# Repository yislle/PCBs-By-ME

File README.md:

# PCBs-By-ME
Proyectos electrónicos

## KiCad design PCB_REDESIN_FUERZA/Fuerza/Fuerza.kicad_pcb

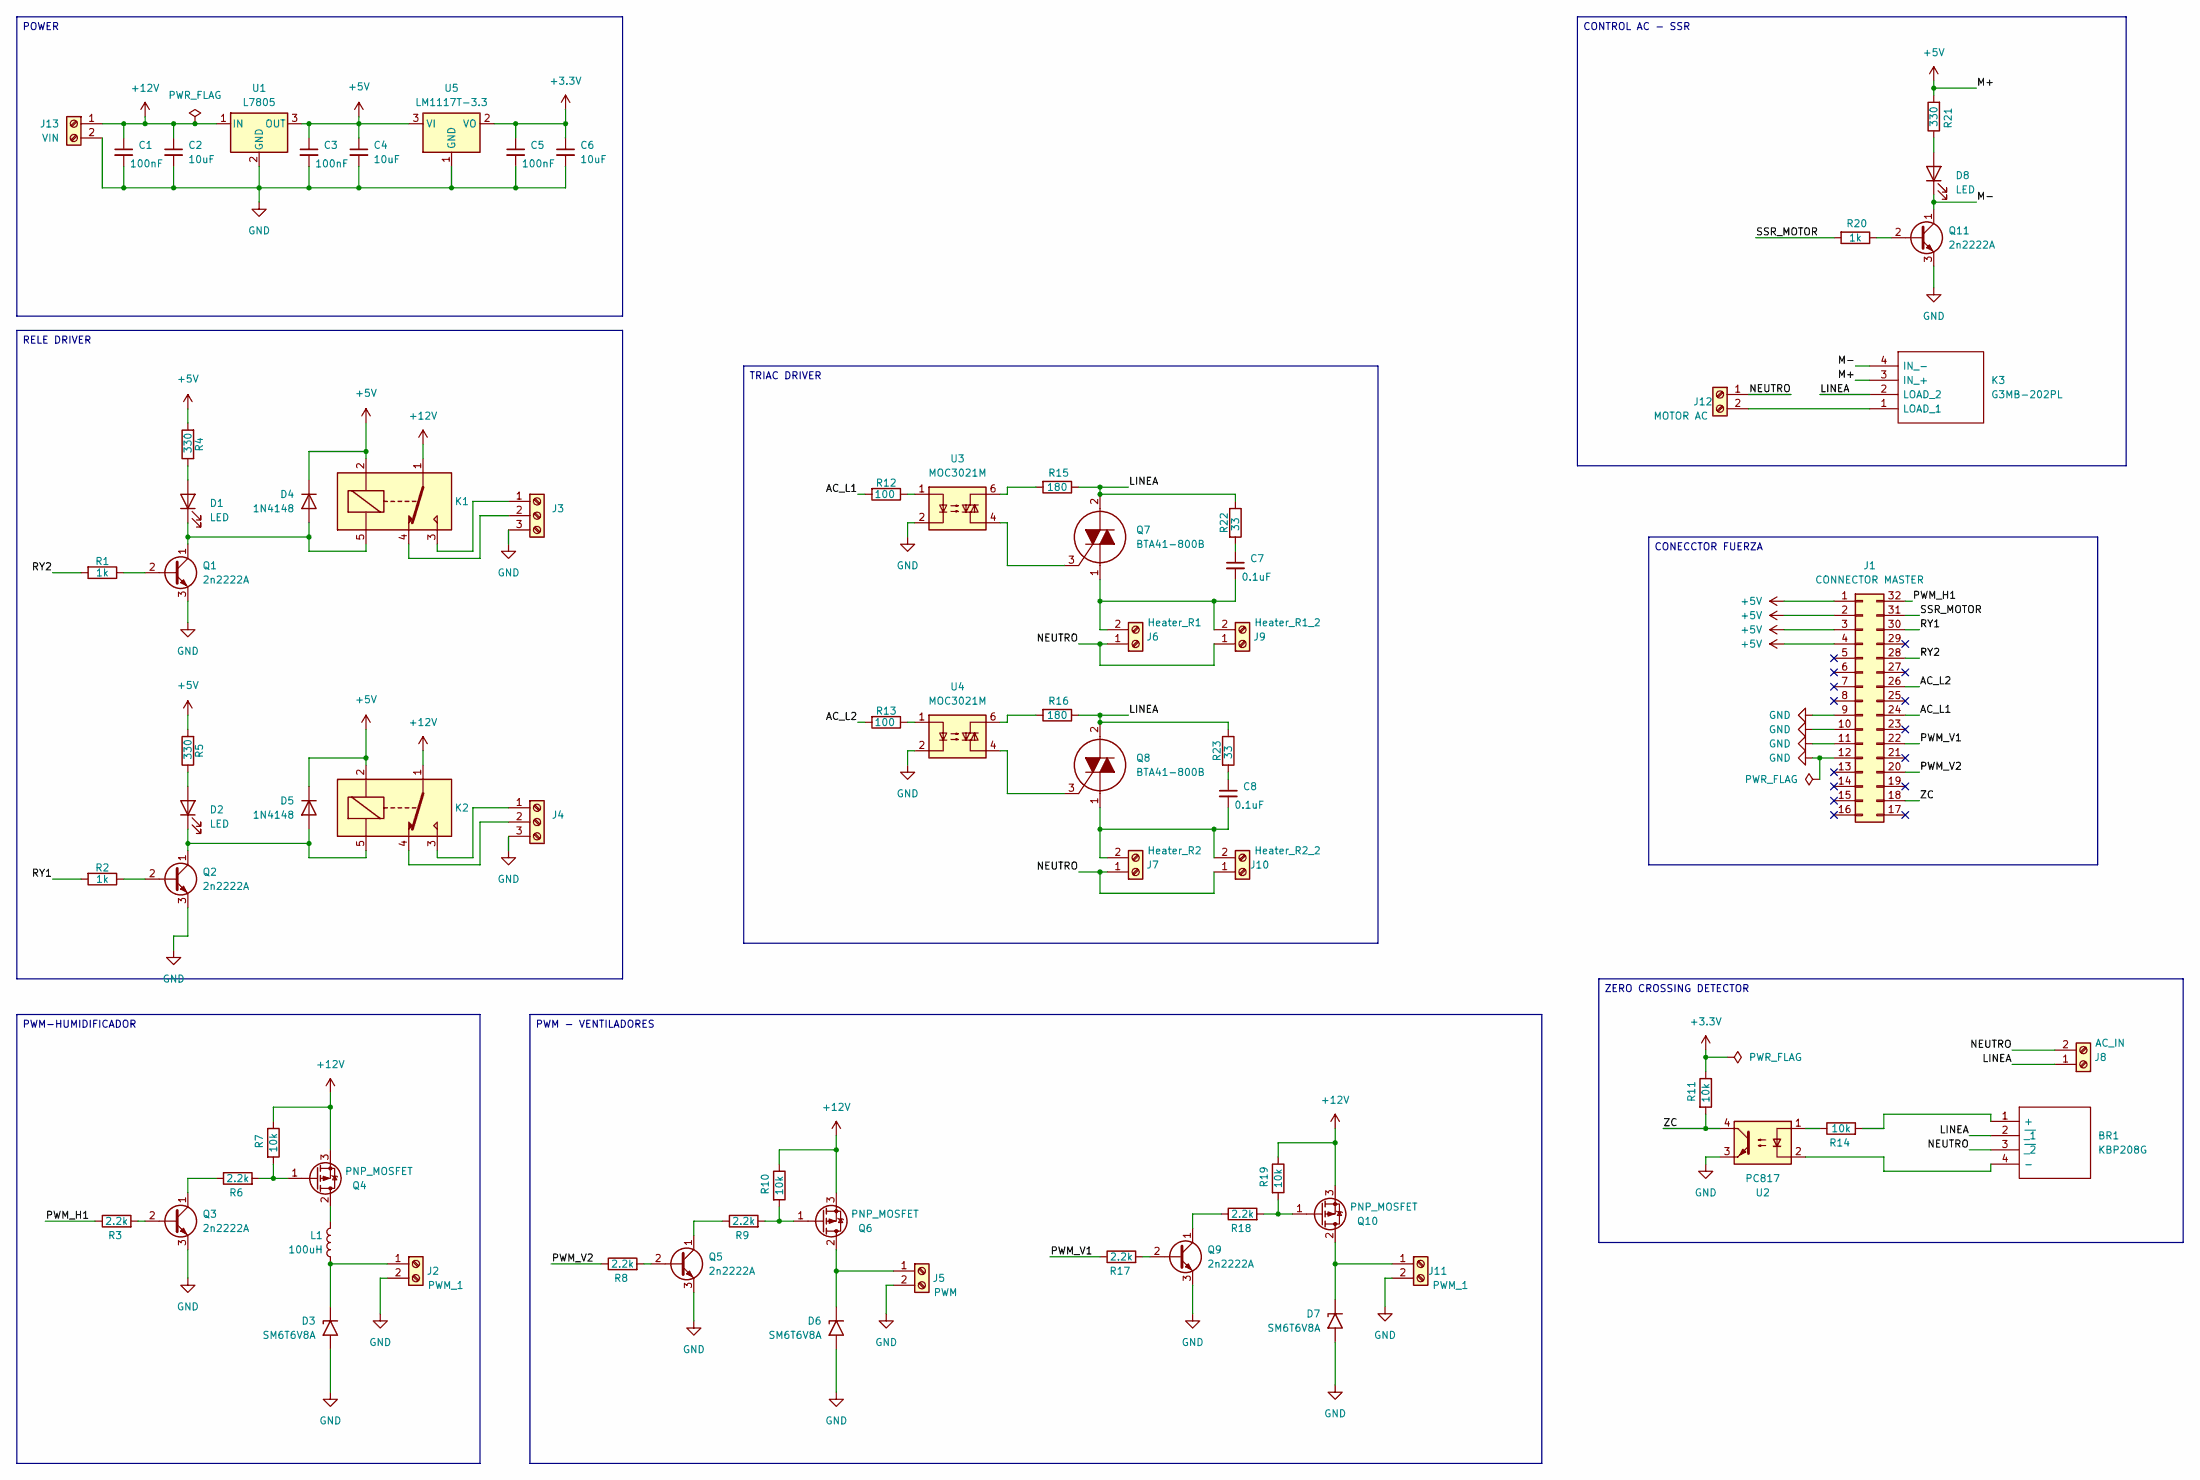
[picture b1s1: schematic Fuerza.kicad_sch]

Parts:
BR1: KBP208G; Manufacturer_Part_Number KBP208G; Mouser Part Number 621-KBP208G
C1, C3, C5: 100nF; C_1206_3216Metric_Pad1.33x1.80mm_HandSolder
C2, C4, C6: 10uF; C_1206_3216Metric_Pad1.33x1.80mm_HandSolder
C7, C8: 0.1uF; C_Rect_L13.0mm_W3.0mm_P10.00mm_FKS3_FKP3_MKS4
D1, D2, D8: LED; LED_1206_3216Metric
D3, D6, D7: SM6T6V8A; D_SMB
D4, D5: 1N4148; D_SMB_Handsoldering
J1: CONNECTOR MASTER; PinHeader_2x16_P2.54mm_Vertical
J2, J11: PWM_1; TerminalBlock_Phoenix_MKDS-1,5-2-5.08_1x02_P5.08mm_Horizont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
J3, J4: Screw_Terminal_01x03; TerminalBlock_MetzConnect_Type011_RT05503HBLC_1x03_P5.00mm_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
J5: PWM; TerminalBlock_Phoenix_MKDS-1,5-2-5.08_1x02_P5.08mm_Horizont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
J6: Heater_R1; NC6P10702
J7: Heater_R2; NC6P10702
J8: AC_IN; NC6P10702
J9: Heater_R1_2; NC6P10702
J10: Heater_R2_2; NC6P10702
J12: MOTOR AC; NC6P10702
J13: VIN; TerminalBlock_Phoenix_MKDS-1,5-2-5.08_1x02_P5.08mm_Horizont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
K1, K2: SANYOU_SRD_Form_C; Relay_SPDT_SANYOU_SRD_Series_Form_C
K3: G3MB-202PL; G3MB202PL; Manufacturer_Part_Number G3MB-202PL
L1: 100uH; L_Sunlord_MWSA0518S
Q1, Q2, Q3, Q5, Q9, Q11: 2n2222A; TO-92_Inline
Q4, Q6, Q10: PNP_MOSFET; TO-252-2
Q7, Q8: BTA41-800B; TO552P460X1530X2215-3P; Manufacturer_Part_Number BTA41-800B; Mouser Part Number N/A
R1, R2, R20: 1k; R_0805_2012Metric
R3, R6, R8, R9, R17, R18: 2.2k; R_0805_2012Metric
R4, R5, R21: 330; R_0805_2012Metric
R7, R10, R11, R14, R19: 10k; R_0805_2012Metric
R12, R13: 100; R_0805_2012Metric
R15, R16: 180; R_Axial_DIN0414_L11.9mm_D4.5mm_P15.24mm_Horizontal
R22, R23: 33; R_Axial_Power_L48.0mm_W12.5mm_P10.16mm_Vertical
U1: L7805; TO-252-2
U2: PC817; DIP-4_W7.62mm
U3, U4: MOC3021M; DIP-6_W7.62mm_Socket_LongPads
U5: LM1117T-3.3; TO-220F-3_Horizontal_TabDown

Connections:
+3.3V: C5.1, C6.1, R11.1, U5.2 (VO)
+5V: C3.1, C4.1, D4.1 (K), D5.1 (K), J1.1, J1.2, J1.3, J1.4, K1.2, K2.2, K3.3 (IN_+), R4.2, R5.2, R21.2, U1.3 (OUT), U5.3 (VI)
+12V: C1.1, C2.1, J13.1, K1.1, K2.1, Q4.3 (S), Q6.3 (S), Q10.3 (S), R7.1, R10.1, R19.1, U1.1 (IN)
/AC_L1: J1.24, R12.2
/AC_L2: J1.26, R13.2
/LINEA: BR1.2 (~_1), J8.1, K3.2 (LOAD_2), Q7.2, Q8.2, R15.1, R16.1, R22.1, R23.1
/M-: D8.1 (K), K3.4 (IN_-), Q11.1 (C)
/NEUTRO: BR1.3 (~_2), J6.1, J7.1, J8.2, J9.1, J10.1, J12.1
/PWM_H1: J1.32, R3.1
/PWM_V1: J1.22, R17.1
/PWM_V2: J1.20, R8.1
/RY1: J1.30, R2.2
/RY2: J1.28, R1.2
/SSR_MOTOR: J1.31, R20.2
/ZC: J1.18, R11.2, U2.4
GND: C1.2, C2.2, C3.2, C4.2, C5.2, C6.2, D3.2 (A2), D6.2 (A2), D7.2 (A2), J1.9, J1.10, J1.11, J1.12, J2.2, J3.3, J4.3, J5.2, J11.2, J13.2, Q1.3 (E), Q2.3 (E), Q3.3 (E), Q5.3 (E), Q9.3 (E), Q11.3 (E), U1.2 (GND), U2.3, U3.2, U4.2, U5.1 (GND)
unnamed: BR1.1 (+), R14.2
unnamed: BR1.4 (-), U2.2
unnamed: C7.1, R22.2
unnamed: C8.1, R23.2
unnamed: D1.2 (A), R4.1
unnamed: D1.1 (K), D4.2 (A), K1.5, Q1.1 (C)
unnamed: D2.2 (A), R5.1
unnamed: D2.1 (K), D5.2 (A), K2.5, Q2.1 (C)
unnamed: D3.1 (A1), J2.1, L1.2
unnamed: D6.1 (A1), J5.1, Q6.2 (D)
unnamed: D7.1 (A1), J11.1, Q10.2 (D)
unnamed: D8.2 (A), R21.1
unnamed: J3.1, K1.3
unnamed: J3.2, K1.4
unnamed: J4.1, K2.3
unnamed: J4.2, K2.4
unnamed: C7.2, J6.2, J9.2, Q7.1
unnamed: C8.2, J7.2, J10.2, Q8.1
unnamed: J12.2, K3.1 (LOAD_1)
unnamed: Q1.2 (B), R1.1
unnamed: Q2.2 (B), R2.1
unnamed: Q3.2 (B), R3.2
unnamed: Q3.1 (C), R6.1
unnamed: L1.1, Q4.2 (D)
unnamed: Q4.1 (G), R6.2, R7.2
unnamed: Q5.2 (B), R8.2
unnamed: Q5.1 (C), R9.1
unnamed: Q6.1 (G), R9.2, R10.2
unnamed: Q7.3, U3.4
unnamed: Q8.3, U4.4
unnamed: Q9.2 (B), R17.2
unnamed: Q9.1 (C), R18.1
unnamed: Q10.1 (G), R18.2, R19.2
unnamed: Q11.2 (B), R20.1
unnamed: R12.1, U3.1
unnamed: R13.1, U4.1
unnamed: R14.1, U2.1
unnamed: R15.2, U3.6
unnamed: R16.2, U4.6

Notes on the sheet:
RELE DRIVER
CONTROL AC - SSR
PWM-HUMIDIFICADOR
ZERO CROSSING DETECTOR
TRIAC DRIVER
CONECCTOR FUERZA
POWER
PWM - VENTILADORES

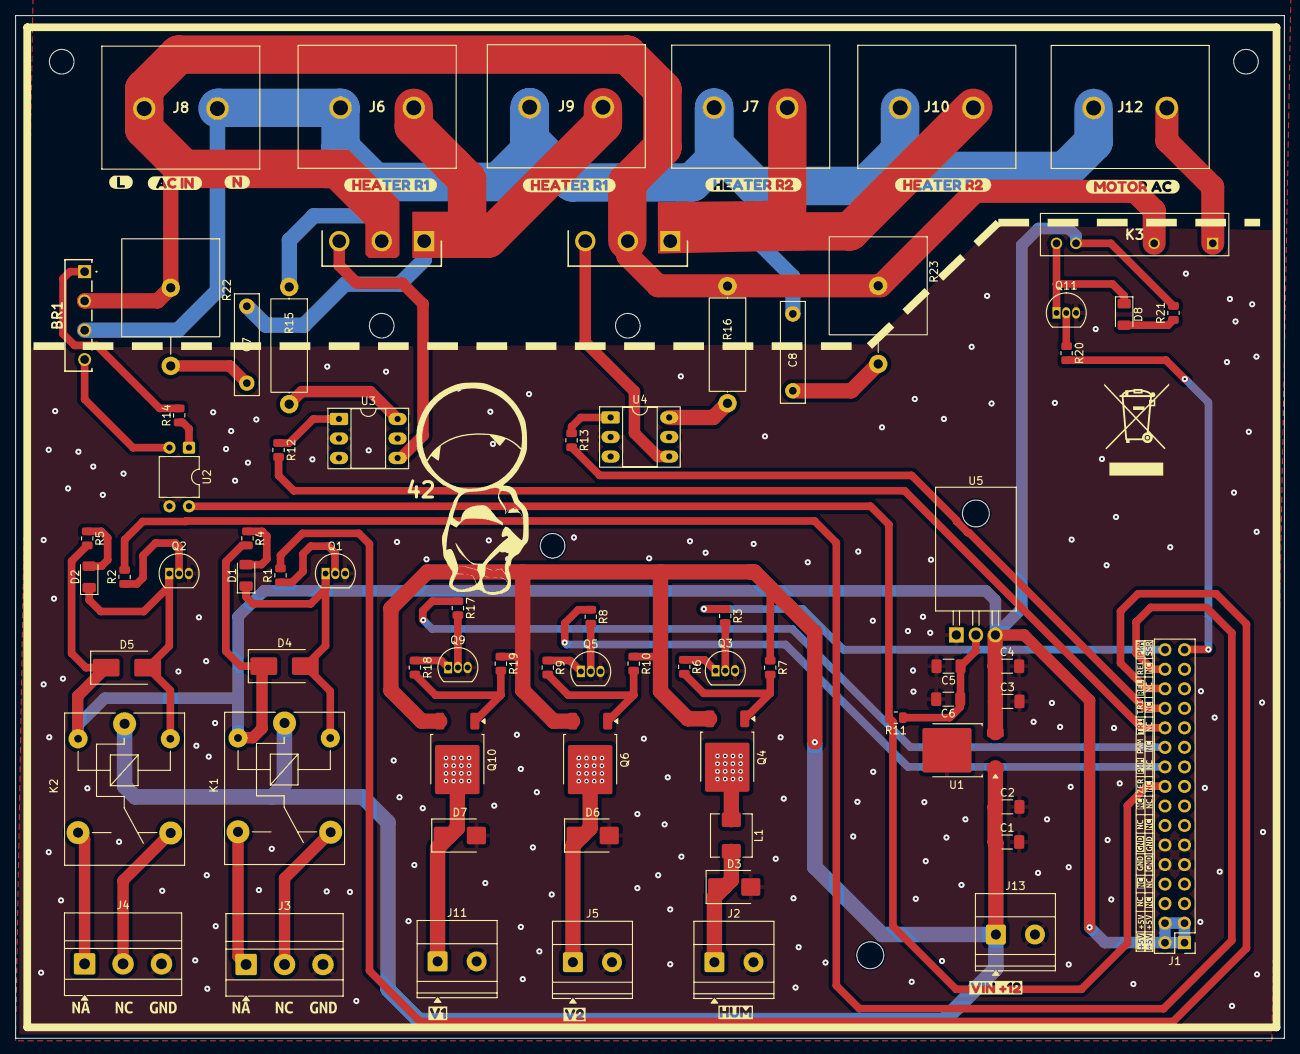
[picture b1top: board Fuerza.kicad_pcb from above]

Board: 2 copper layers, 165.0 x 133.0 mm, 124 parts (0 on the bottom side), 55 nets.

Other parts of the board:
42: LOGO
kibuzzard-6933B8AD, kibuzzard-6933B8AD#2: G***; kibuzzard-6933B8AD
kibuzzard-6933B8B3, kibuzzard-6933B8B3#2: G***; kibuzzard-6933B8B3
kibuzzard-6933B8C0, kibuzzard-6933B8C0#2: G***; kibuzzard-6933B8C0
kibuzzard-69101CAE, kibuzzard-69101CAE#2: G***; kibuzzard-69101CAE
kibuzzard-69101CCC, kibuzzard-69101CCC#2, kibuzzard-69101CCC#3, kibuzzard-69101CCC#4, kibuzzard-69101CCC#5, kibuzzard-69101CCC#6, kibuzzard-69101CCC#7: G***; kibuzzard-69101CCC
kibuzzard-69101D02: G***; kibuzzard-69101D02
kibuzzard-69101D2A, kibuzzard-69101D2A#2, kibuzzard-69101D2A#3, kibuzzard-69101D2A#4, kibuzzard-69101D2A#5, kibuzzard-69101D2A#6, kibuzzard-69101D2A#7, kibuzzard-69101D2A#8: G***; kibuzzard-69101D2A
kibuzzard-69101D16: G***; kibuzzard-69101D16
kibuzzard-69101D36: G***; kibuzzard-69101D36
kibuzzard-69101DDA: G***; kibuzzard-69101DDA
kibuzzard-69101DF9: G***; kibuzzard-69101DF9
kibuzzard-69101E1F: G***; kibuzzard-69101E1F
kibuzzard-69101E3D: G***; kibuzzard-69101E3D
kibuzzard-69101E6F: G***; kibuzzard-69101E6F
kibuzzard-69101ED2, kibuzzard-69101ED2#2: G***; kibuzzard-69101ED2
kibuzzard-69101EFC, kibuzzard-69101EFC#2: G***; kibuzzard-69101EFC
kibuzzard-69102CE6: G***; kibuzzard-69102CE6
kibuzzard-693906A7: G***; kibuzzard-693906A7
kibuzzard-693907B1: G***; kibuzzard-693907B1
kibuzzard-693907E1: G***; kibuzzard-693907E1
kibuzzard-693907F7: G***; kibuzzard-693907F7
kibuzzard-6910205B, kibuzzard-6910205B#2: G***; kibuzzard-6910205B
kibuzzard-6939064C: G***; kibuzzard-6939064C
kibuzzard-6939067E: G***; kibuzzard-6939067E
kibuzzard-6939072C: G***; kibuzzard-6939072C
kibuzzard-6939079C: G***; kibuzzard-6939079C
kibuzzard-69390653: G***; kibuzzard-69390653
kibuzzard-69390751, kibuzzard-69390751#2: G***; kibuzzard-69390751
kibuzzard-69390791: G***; kibuzzard-69390791

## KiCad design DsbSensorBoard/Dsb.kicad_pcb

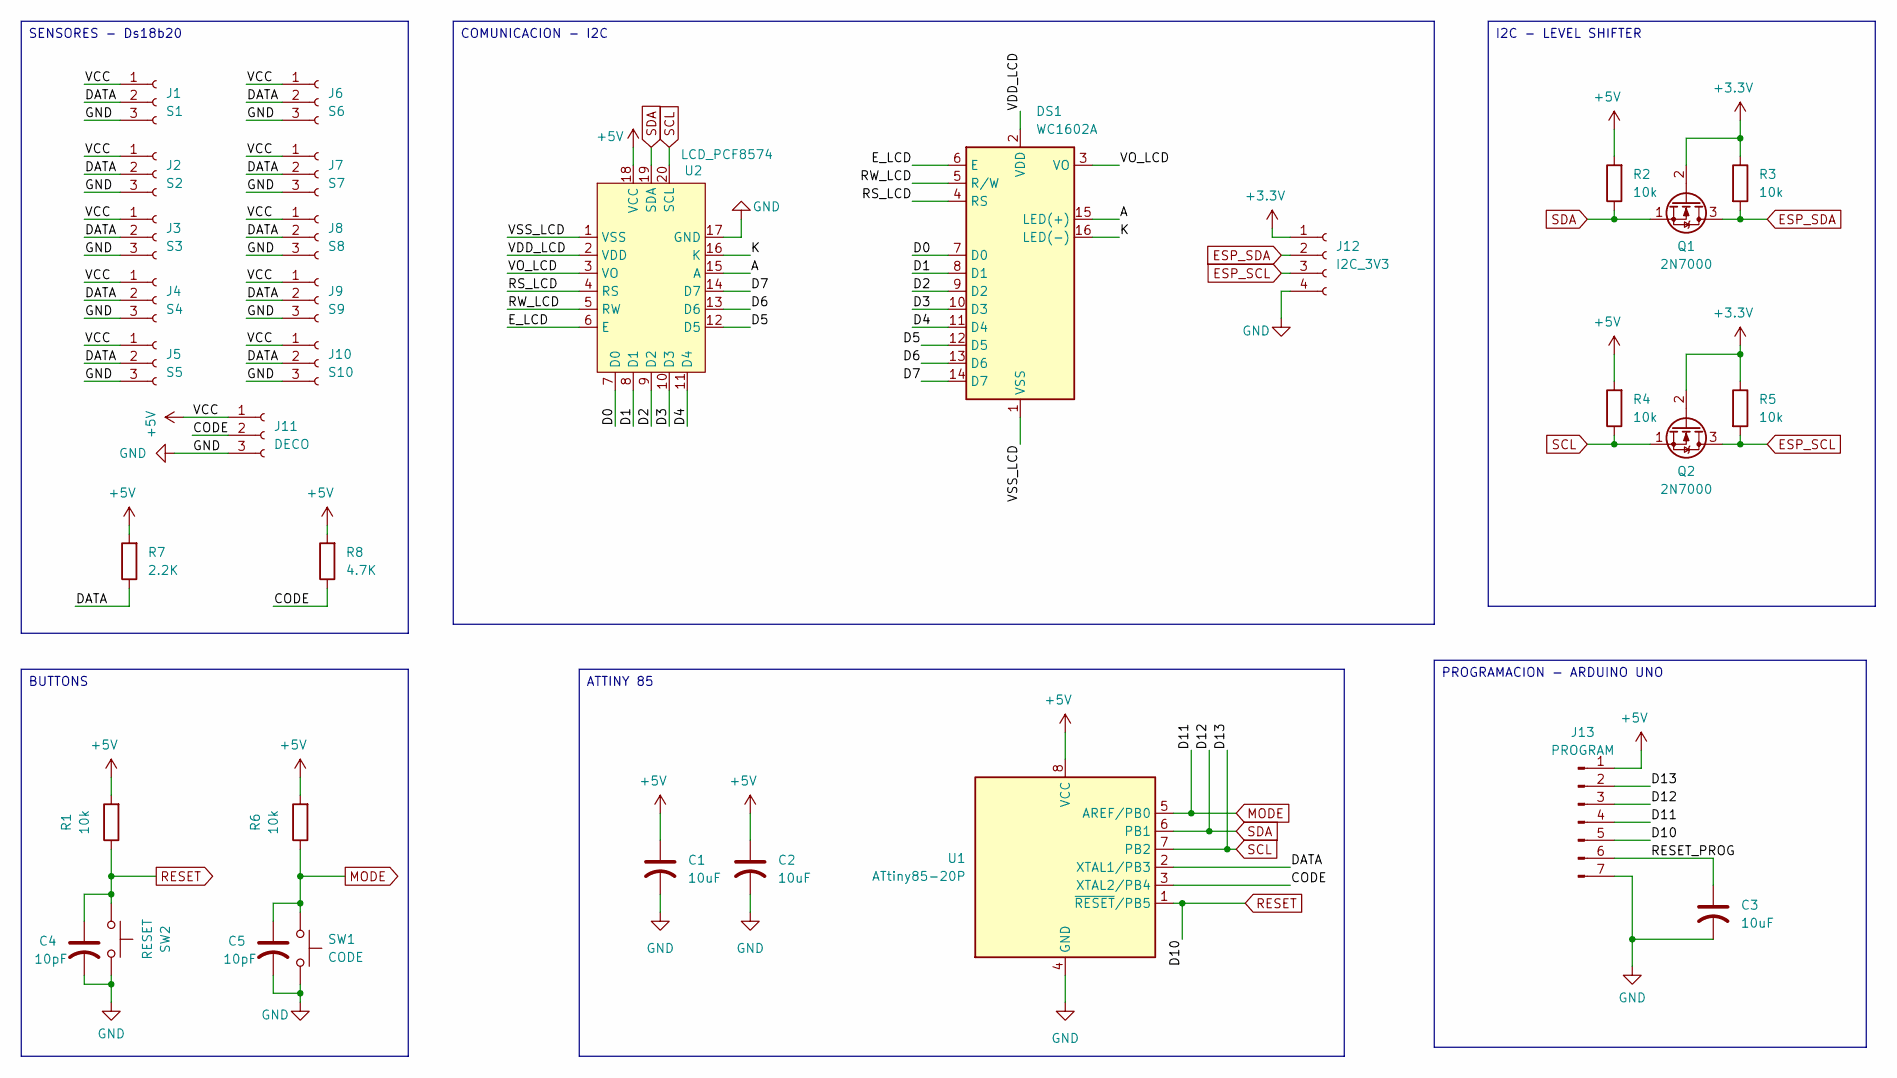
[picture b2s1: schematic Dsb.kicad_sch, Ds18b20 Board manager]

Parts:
C1, C2, C3: 10uF; CP_Radial_D6.3mm_P2.50mm
C4, C5: 10pF; C_Disc_D3.0mm_W1.6mm_P2.50mm
DS1: WC1602A
J1: S1; JST_EH_B3B-EH-A_1x03_P2.50mm_Vertical
J2: S2; JST_EH_B3B-EH-A_1x03_P2.50mm_Vertical
J3: S3; JST_EH_B3B-EH-A_1x03_P2.50mm_Vertical
J4: S4; JST_EH_B3B-EH-A_1x03_P2.50mm_Vertical
J5: S5; JST_EH_B3B-EH-A_1x03_P2.50mm_Vertical
J6: S6; JST_EH_B3B-EH-A_1x03_P2.50mm_Vertical
J7: S7; JST_EH_B3B-EH-A_1x03_P2.50mm_Vertical
J8: S8; JST_EH_B3B-EH-A_1x03_P2.50mm_Vertical
J9: S9; JST_EH_B3B-EH-A_1x03_P2.50mm_Vertical
J10: S10; JST_EH_B3B-EH-A_1x03_P2.50mm_Vertical
J11: DECO; JST_EH_B3B-EH-A_1x03_P2.50mm_Vertical
J12: I2C_3V3; JST_EH_B4B-EH-A_1x04_P2.50mm_Vertical
J13: PROGRAM; PinHeader_1x07_P2.54mm_Vertical
Q1, Q2: 2N7000; TO-92
R1, R2, R3, R4, R5, R6: 10k; R_Axial_DIN0207_L6.3mm_D2.5mm_P15.24mm_Horizontal
R7: 2.2K; R_Axial_DIN0207_L6.3mm_D2.5mm_P15.24mm_Horizontal
R8: 4.7K; R_Axial_DIN0207_L6.3mm_D2.5mm_P15.24mm_Horizontal
SW1: CODE; SW_PUSH_6mm_H4.3mm
SW2: RESET; SW_PUSH_6mm_H4.3mm
U1: ATtiny85-20P; DIP-8_W7.62mm_LongPads
U2: LCD_PCF8574

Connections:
+3.3V: J12.1, Q1.2 (G), Q2.2 (G), R3.1, R5.1
+5V: C1.1, C2.1, J1.1, J2.1, J3.1, J4.1, J5.1, J6.1, J7.1, J8.1, J9.1, J10.1, J11.1, J13.1, R1.2, R2.2, R4.2, R6.2, R7.2, R8.2, U1.8 (VCC), U2.18 (VCC)
/A: DS1.15 (LED(+)), U2.15 (A)
/CODE: J11.2, R8.1, U1.3 (XTAL2/PB4)
/D0: DS1.7 (D0), U2.7 (D0)
/D1: DS1.8 (D1), U2.8 (D1)
/D2: DS1.9 (D2), U2.9 (D2)
/D3: DS1.10 (D3), U2.10 (D3)
/D4: DS1.11 (D4), U2.11 (D4)
/D5: DS1.12 (D5), U2.12 (D5)
/D6: DS1.13 (D6), U2.13 (D6)
/D7: DS1.14 (D7), U2.14 (D7)
/DATA: J1.2, J2.2, J3.2, J4.2, J5.2, J6.2, J7.2, J8.2, J9.2, J10.2, R7.1, U1.2 (XTAL1/PB3)
/E_LCD: DS1.6 (E), U2.6 (E)
/K: DS1.16 (LED(-)), U2.16 (K)
/RESET_PROG: C3.1, J13.6
/RS_LCD: DS1.4 (RS), U2.4 (RS)
/RW_LCD: DS1.5 (R/W), U2.5 (RW)
/VDD_LCD: DS1.2 (VDD), U2.2 (VDD)
/VO_LCD: DS1.3 (VO), U2.3 (VO)
/VSS_LCD: DS1.1 (VSS), U2.1 (VSS)
ESP_SCL: J12.3, Q2.3 (D), R5.2
ESP_SDA: J12.2, Q1.3 (D), R3.2
GND: C1.2, C2.2, C3.2, C4.2, C5.2, J1.3, J2.3, J3.3, J4.3, J5.3, J6.3, J7.3, J8.3, J9.3, J10.3, J11.3, J12.4, J13.7, SW1.2, SW2.1, U1.4 (GND), U2.17 (GND)
MODE: C5.1, J13.4, R6.1, SW1.1, U1.5 (AREF/PB0)
RESET: C4.1, J13.5, R1.1, SW2.2, U1.1 (~RESET/PB5)
SCL: J13.2, Q2.1 (S), R4.1, U1.7 (PB2), U2.20 (SCL)
SDA: J13.3, Q1.1 (S), R2.1, U1.6 (PB1), U2.19 (SDA)

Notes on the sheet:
SENSORES - Ds18b20
ATTINY 85
PROGRAMACION - ARDUINO UNO
BUTTONS
I2C - LEVEL SHIFTER
COMUNICACION - I2C

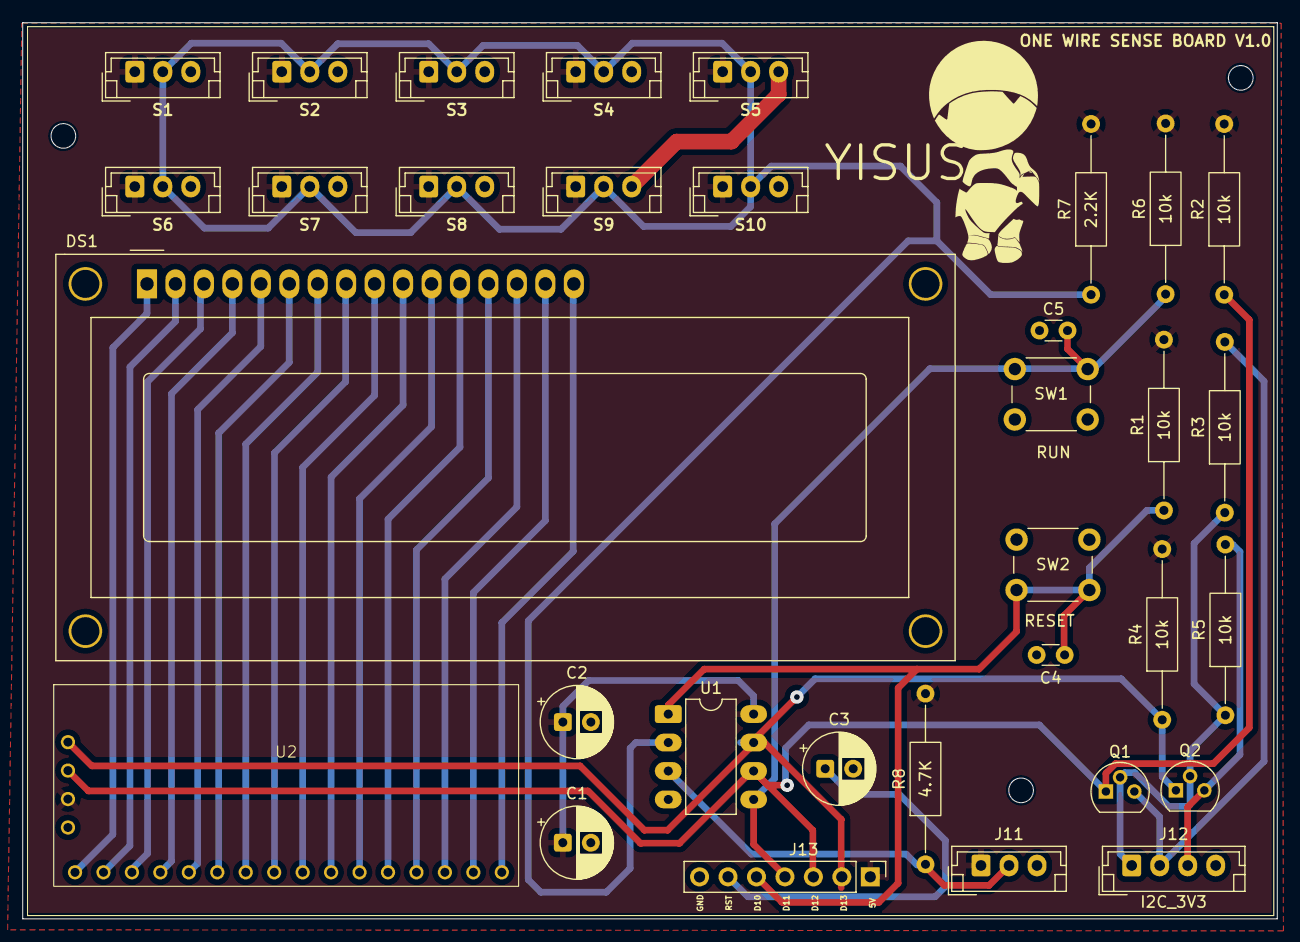
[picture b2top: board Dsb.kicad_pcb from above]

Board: 2 copper layers, 112.0 x 80.0 mm, 34 parts (0 on the bottom side), 28 nets.

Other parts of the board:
YISUS: LOGO

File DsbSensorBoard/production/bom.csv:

Designator,Footprint,Quantity,Value,LCSC Part #
"C1, C2, C3",CP_Radial_D6.3mm_P2.50mm,3,10uF,
"C4, C5",C_Disc_D3.0mm_W1.6mm_P2.50mm,2,10pF,
DS1,WC1602A,1,WC1602A,
J1,JST_EH_B3B-EH-A_1x03_P2.50mm_Vertical,1,S1,
J10,JST_EH_B3B-EH-A_1x03_P2.50mm_Vertical,1,S10,
J11,JST_EH_B3B-EH-A_1x03_P2.50mm_Vertical,1,DECO,
J12,JST_EH_B4B-EH-A_1x04_P2.50mm_Vertical,1,I2C_3V3,
J13,PinHeader_1x07_P2.54mm_Vertical,1,PROGRAM,
J2,JST_EH_B3B-EH-A_1x03_P2.50mm_Vertical,1,S2,
J3,JST_EH_B3B-EH-A_1x03_P2.50mm_Vertical,1,S3,
J4,JST_EH_B3B-EH-A_1x03_P2.50mm_Vertical,1,S4,
J5,JST_EH_B3B-EH-A_1x03_P2.50mm_Vertical,1,S5,
J6,JST_EH_B3B-EH-A_1x03_P2.50mm_Vertical,1,S6,
J7,JST_EH_B3B-EH-A_1x03_P2.50mm_Vertical,1,S7,
J8,JST_EH_B3B-EH-A_1x03_P2.50mm_Vertical,1,S8,
J9,JST_EH_B3B-EH-A_1x03_P2.50mm_Vertical,1,S9,
"Q1, Q2",TO-92,2,2N7000,
"R1, R2, R3, R4, R5, R6",R_Axial_DIN0207_L6.3mm_D2.5mm_P15.24mm_Horizontal,6,10k,
R7,R_Axial_DIN0207_L6.3mm_D2.5mm_P15.24mm_Horizontal,1,2.2K,
R8,R_Axial_DIN0207_L6.3mm_D2.5mm_P15.24mm_Horizontal,1,4.7K,
SW1,SW_PUSH_6mm_H4.3mm,1,RUN,
SW2,SW_PUSH_6mm_H4.3mm,1,RESET,
U1,DIP-8_W7.62mm_LongPads,1,ATtiny85-20P,
U2,LCD_PCF8574,1,LCD_PCF8574,

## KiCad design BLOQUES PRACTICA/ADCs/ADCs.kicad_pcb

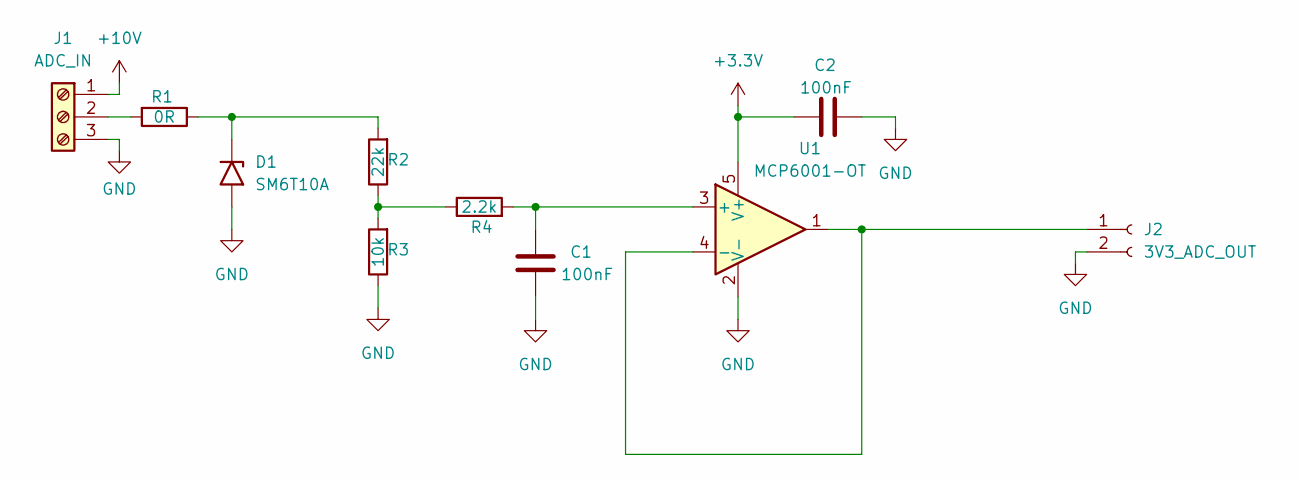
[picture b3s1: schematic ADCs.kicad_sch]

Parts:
C1, C2: 100nF; C_1206_3216Metric
D1: SM6T10A; D_SMB
J1: ADC_IN; TerminalBlock_Xinya_XY308-2.54-3P_1x03_P2.54mm_Horizontal
J2: 3V3_ADC_OUT; JST_XH_S2B-XH-A-1_1x02_P2.50mm_Horizontal
R1: 0R; R_0805_2012Metric
R2: 22k; R_0805_2012Metric
R3: 10k; R_0805_2012Metric
R4: 2.2k; R_0805_2012Metric
U1: MCP6001-OT; SOT-23-5

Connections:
+3.3V: C2.1, U1.5 (V+)
+10V: J1.1
GND: C1.2, C2.2, D1.2 (A2), J1.3, J2.2, R3.1, U1.2 (V-)
unnamed: D1.1 (A1), R1.1, R2.2
unnamed: J1.2, R1.2
unnamed: J2.1, U1.1, U1.4 (-)
unnamed: R2.1, R3.2, R4.1
unnamed: C1.1, R4.2, U1.3 (+)

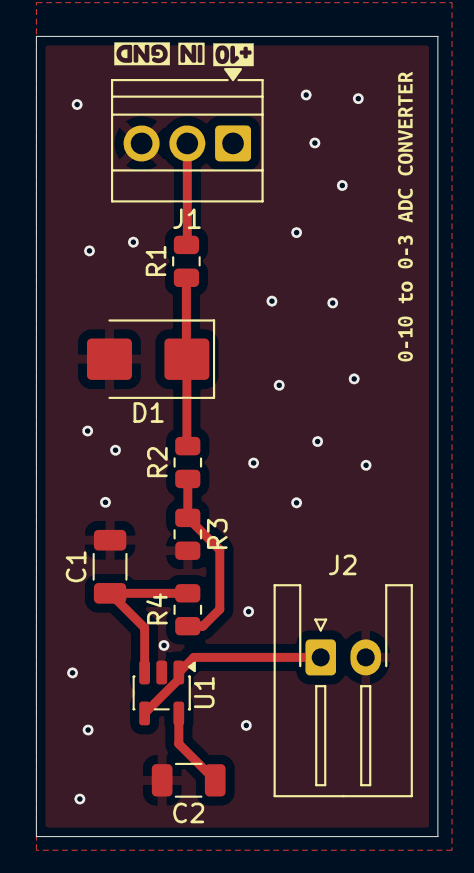
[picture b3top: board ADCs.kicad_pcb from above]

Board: 2 copper layers, 22.3 x 44.4 mm, 14 parts (0 on the bottom side), 7 nets.

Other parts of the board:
kibuzzard-693DC0A2: G***; kibuzzard-693DC0A2
kibuzzard-693DC08C: G***; kibuzzard-693DC08C
kibuzzard-693DC098: G***; kibuzzard-693DC098
kibuzzard-69406A88: G***; kibuzzard-69406A88
